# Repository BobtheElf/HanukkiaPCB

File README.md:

# HanukkiaPCB
This is a PCB I designed on Eagle for my family and all of the good people at Mines Hillel. All of this is free to use and I encourage better designs. I used AutoCad Eagle to design the schematic and PCB, but if you would like to print the board as-is, I have included the most current gerber files.

## More Details
This circuit is based off Dr. Chris Coulston's VU-meter circuit, and should only need a 5V USB-C power source to work. Simply plug in the board with appropriate parts soldered, and turn the potentiometer to the correct day of Hanukkah. Beware that different batches of LM324 op-amps can misbehave in this circuit.

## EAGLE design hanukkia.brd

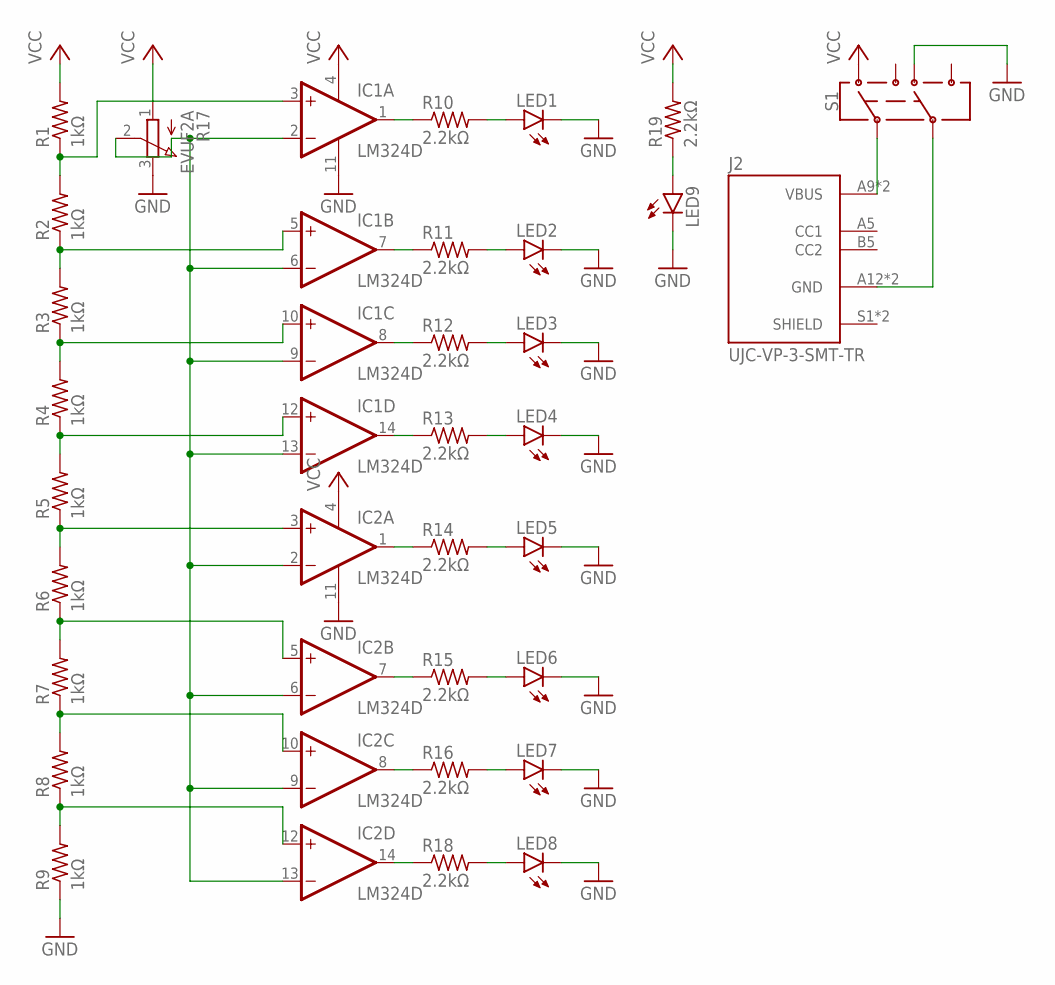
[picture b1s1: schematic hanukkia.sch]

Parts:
IC1, IC2: LM324D; SO14
J2: UJC-VP-3-SMT-TR; CUI_UJC-VP-3-SMT-TR
LED1, LED2, LED3, LED4, LED5, LED6, LED7, LED8, LED9: LEDCHIPLED_1206; CHIPLED_1206
R1, R2, R3, R4, R5, R6, R7, R8, R9: 1kΩ; R1206
R10, R11, R12, R13, R14, R15, R16, R18, R19: 2.2kΩ; R1206
R17: EVUF2A; EVUF
S1: SWITCH-DPDT-SMD-AYZ0202; SWITCH_DPDT_SMD_AYZ0202

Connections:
GND: IC1.11 (V-), IC2.11 (V-), LED1.C, LED2.C, LED3.C, LED4.C, LED5.C, LED6.C, LED7.C, LED8.C, LED9.C, R9.1, R17.3 (E), S1.6
unnamed: IC1.3 (+IN), R1.1, R2.2
unnamed: IC1.5 (+IN), R2.1, R3.2
unnamed: IC1.10 (+IN), R3.1, R4.2
unnamed: IC1.12 (+IN), R4.1, R5.2
unnamed: IC2.3 (+IN), R5.1, R6.2
unnamed: IC2.5 (+IN), R6.1, R7.2
unnamed: IC2.10 (+IN), R7.1, R8.2
unnamed: IC2.12 (+IN), R8.1, R9.2
unnamed: IC1.2 (-IN), IC1.6 (-IN), IC1.9 (-IN), IC1.13 (-IN), IC2.2 (-IN), IC2.6 (-IN), IC2.9 (-IN), IC2.13 (-IN), R17.2 (S)
unnamed: IC1.1 (OUT), R10.1
unnamed: LED1.A, R10.2
unnamed: LED2.A, R11.2
unnamed: IC1.7 (OUT), R11.1
unnamed: IC1.8 (OUT), R12.1
unnamed: LED3.A, R12.2
unnamed: IC1.14 (OUT), R13.1
unnamed: LED4.A, R13.2
unnamed: IC2.1 (OUT), R14.1
unnamed: LED5.A, R14.2
unnamed: IC2.7 (OUT), R15.1
unnamed: LED6.A, R15.2
unnamed: IC2.8 (OUT), R16.1
unnamed: LED7.A, R16.2
unnamed: IC2.14 (OUT), R18.1
unnamed: LED8.A, R18.2
unnamed: LED9.A, R19.1
unnamed: J2.A9 (VBUS), J2.B9 (VBUS), S1.2
unnamed: J2.A12 (GND), J2.B12 (GND), S1.5
VCC: IC1.4 (V+), IC2.4 (V+), R1.2, R17.1 (A), R19.2, S1.3

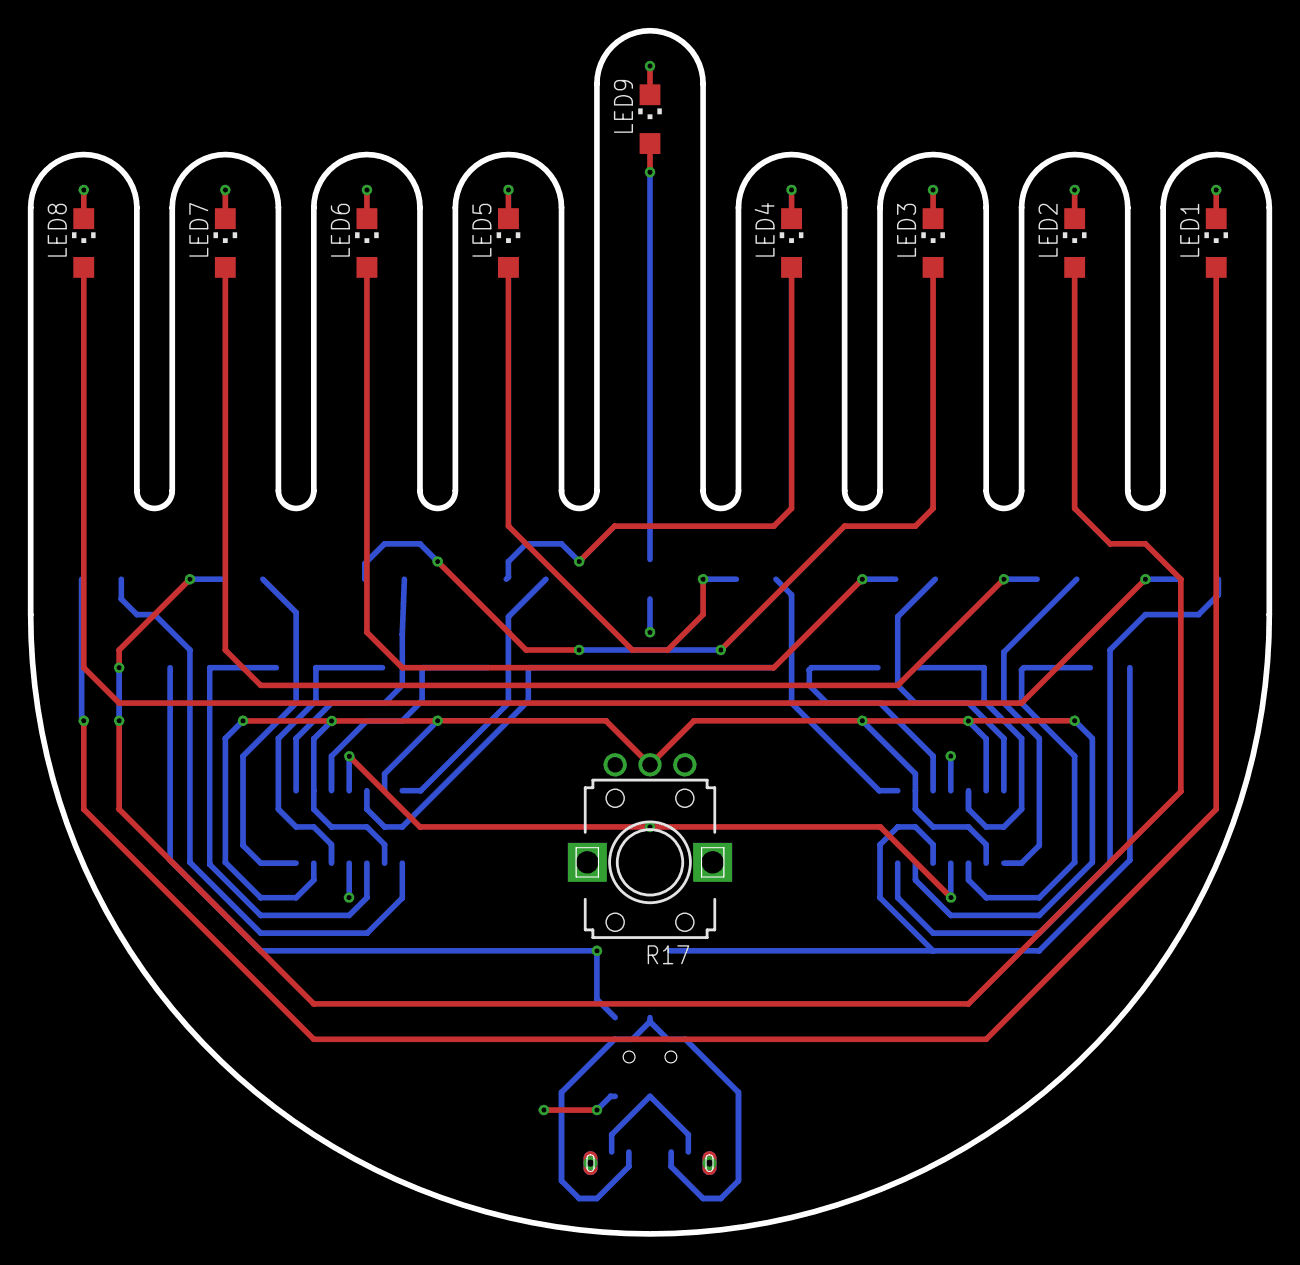
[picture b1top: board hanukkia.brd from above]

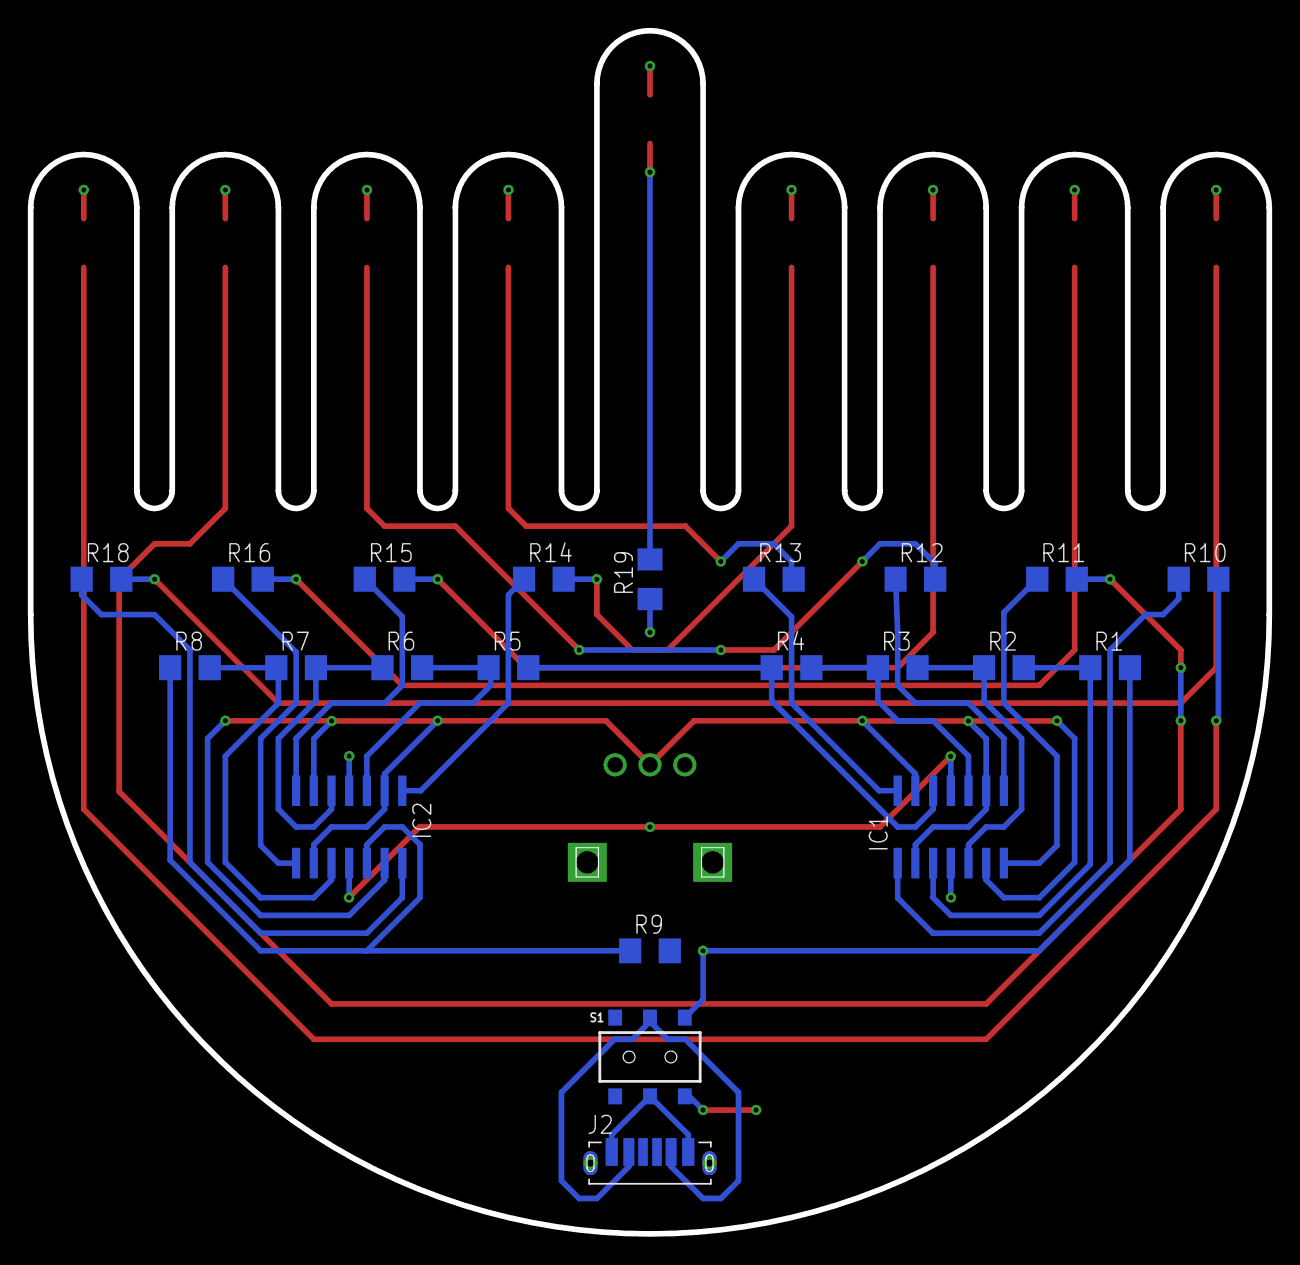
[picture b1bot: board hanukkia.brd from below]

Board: 2 copper layers, 88.9 x 86.4 mm, 32 parts (22 on the bottom side), 30 nets.

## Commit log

2025-01-30 Updated README and added brd, sch, and gerber files
2025-01-30 README fix

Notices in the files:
parts and their libraries:
SparkFun-Switches: Licensing: Creative Commons ShareAlike 4.0 International - https://creativecommons.org/licenses/by-sa/4.0
